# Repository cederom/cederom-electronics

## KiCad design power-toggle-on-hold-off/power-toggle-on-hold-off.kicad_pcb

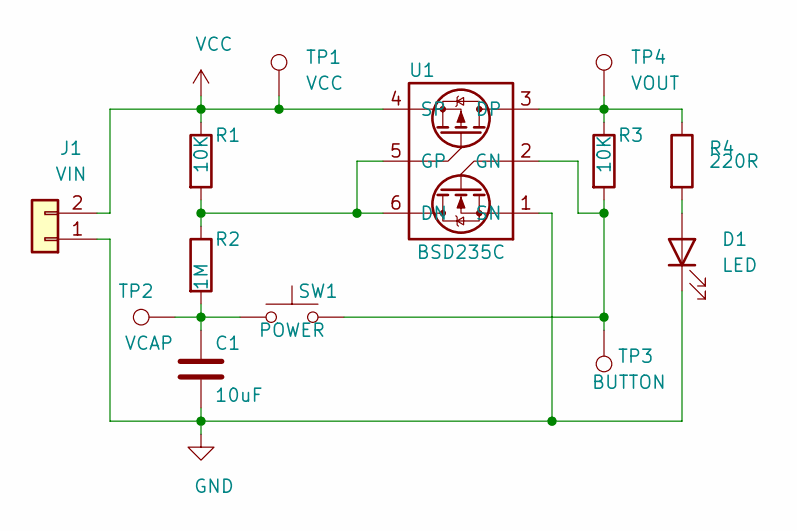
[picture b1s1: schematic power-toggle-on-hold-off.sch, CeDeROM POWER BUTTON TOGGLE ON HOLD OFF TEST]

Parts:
C1: 10uF; C_0805_2012Metric_Pad1.15x1.40mm_HandSolder
D1: LED; D_0805_2012Metric_Pad1.15x1.40mm_HandSolder
J1: VIN; PinHeader_1x02_P2.54mm_Vertical
R1, R3: 10K; R_0603_1608Metric_Pad1.05x0.95mm_HandSolder
R2: 1M; R_0603_1608Metric_Pad1.05x0.95mm_HandSolder
R4: 220R; R_0603_1608Metric_Pad1.05x0.95mm_HandSolder
SW1: POWER; SW_SPST_EVQP0
TP1: VCC; TestPoint_Pad_D2.0mm
TP2: VCAP; TestPoint_Pad_D2.0mm
TP3: BUTTON; TestPoint_Pad_D2.0mm
TP4: VOUT; TestPoint_Pad_D2.0mm
U1: BSD235C; SOT-363_SC-70-6_Handsoldering

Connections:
GND: C1.2, D1.1 (K), J1.1, U1.1 (SN)
unnamed: C1.1, R2.2, SW1.1, TP2.1
unnamed: D1.2 (A), R4.2
unnamed: R1.2, R2.1, U1.5 (GP), U1.6 (DN)
unnamed: R3.1, R4.1, TP4.1, U1.3 (DP)
unnamed: R3.2, SW1.2, TP3.1, U1.2 (GN)
VCC: J1.2, R1.1, TP1.1, U1.4 (SP)

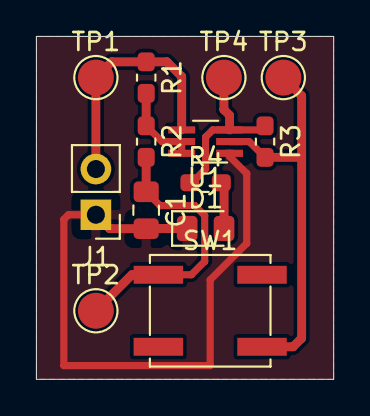
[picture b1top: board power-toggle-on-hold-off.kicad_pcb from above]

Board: 2 copper layers, 16.5 x 19.0 mm, 13 parts (0 on the bottom side), 7 nets.

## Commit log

2020-08-27 Added example power on/off circuit and KiCAD libraries.
2020-09-01 Updated on-off schematics for verification, last one did not work :-)
2020-09-01 Updated BSD235C symbol.
2020-09-01 Added A2235-H symbol.
    Lantronix GPS receiver using SiRFstarIV technology with integrated antena.
2020-09-01 Added Bosch_LGA-10_2x2mm_P0.275x0.250mm.kicad_mod foorptint.
    This is footprint for Bosch BMP388 pressure and temperature sensor.
2020-09-01 Added Bosch's BMP388 pressure and temperature sensfor symbol.
2020-09-01 Single symbols and footprints moved to a bundle.
    * CeDeROM-KiCAD-SYMBOLS.
    * CeDeROM-KiCAD-FOOTPRINTS.
